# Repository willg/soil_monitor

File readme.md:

# Soil Monitor
Three different probes to monitor the moisture of soil by measuring the
capacitance.  

# Probe Testing

Connected multimeter to the 3 different probe designs as follows:

Extech 470 -> dual banana jack -> ~6" dupont M-F hookup wire -> header on
probe soldered to `In+` and `GND`.  This setup with no probe measured 0.18nF.

| Measurement | Design A | Design B | Design C
| ---         | ---      | ---      | ---       |
| Free Space | 0.19 nF  |  0.19 nF | 0.22 nF
| Water |     0.75 nF    |  0.90 nF | 0.83 nF
| Delta | 0.56 nF | 0.71 nF | 0.61 nF

## CAM
To generate gerbers download
[kicad-util](https://gitlab.com/dren.dk/kicad-util) and run the following to
add mouse bites where the lines on `Eco1.User`.  
```
java -jar kicadutil.jar pcb
--file=soil_monitor.kicad_pcb panel --fillet=1
```

This will create the file `output.soil_monitor.kicad_pcb` from which the
gerbers are created

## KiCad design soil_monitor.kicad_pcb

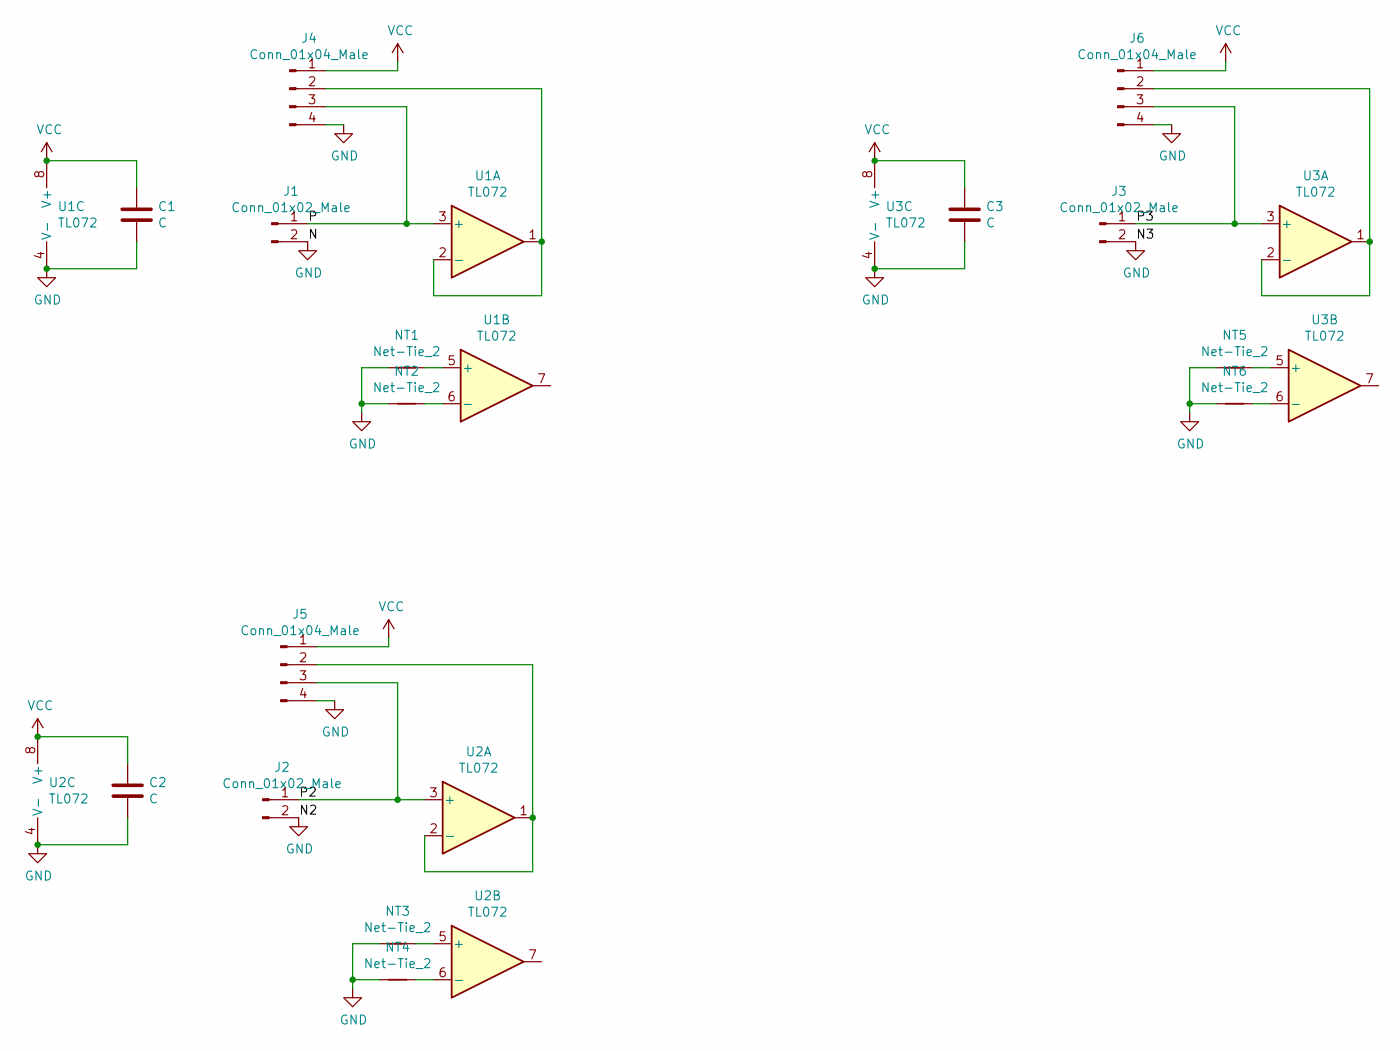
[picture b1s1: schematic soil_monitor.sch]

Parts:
C1, C2, C3: C; C_0805_2012Metric
J1, J2, J3: Conn_01x02_Male; PinHeader_1x02_P2.54mm_Vertical
J4, J5, J6: Conn_01x04_Male; PinSocket_1x04_P2.54mm_Vertical
NT1, NT2, NT3, NT4, NT5, NT6: Net-Tie_2; NetTie-2_SMD_Pad0.5mm
U1, U2, U3: TL072; DIP-8_W7.62mm

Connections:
/P: J1.1, J4.3, U1.3 (+)
/P2: J2.1, J5.3, U2.3 (+)
/P3: J3.1, J6.3, U3.3 (+)
GND: C1.2, C2.2, C3.2, J1.2, J2.2, J3.2, J4.4, J5.4, J6.4, NT1.1, NT2.1, NT3.1, NT4.1, NT5.1, NT6.1, U1.4 (V-), U2.4 (V-), U3.4 (V-)
unnamed: J4.2, U1.1, U1.2 (-)
unnamed: J5.2, U2.1, U2.2 (-)
unnamed: J6.2, U3.1, U3.2 (-)
unnamed: NT1.2, U1.5 (+)
unnamed: NT2.2, U1.6 (-)
unnamed: NT3.2, U2.5 (+)
unnamed: NT4.2, U2.6 (-)
unnamed: NT5.2, U3.5 (+)
unnamed: NT6.2, U3.6 (-)
VCC: C1.1, C2.1, C3.1, J4.1, J5.1, J6.1, U1.8 (V+), U2.8 (V+), U3.8 (V+)

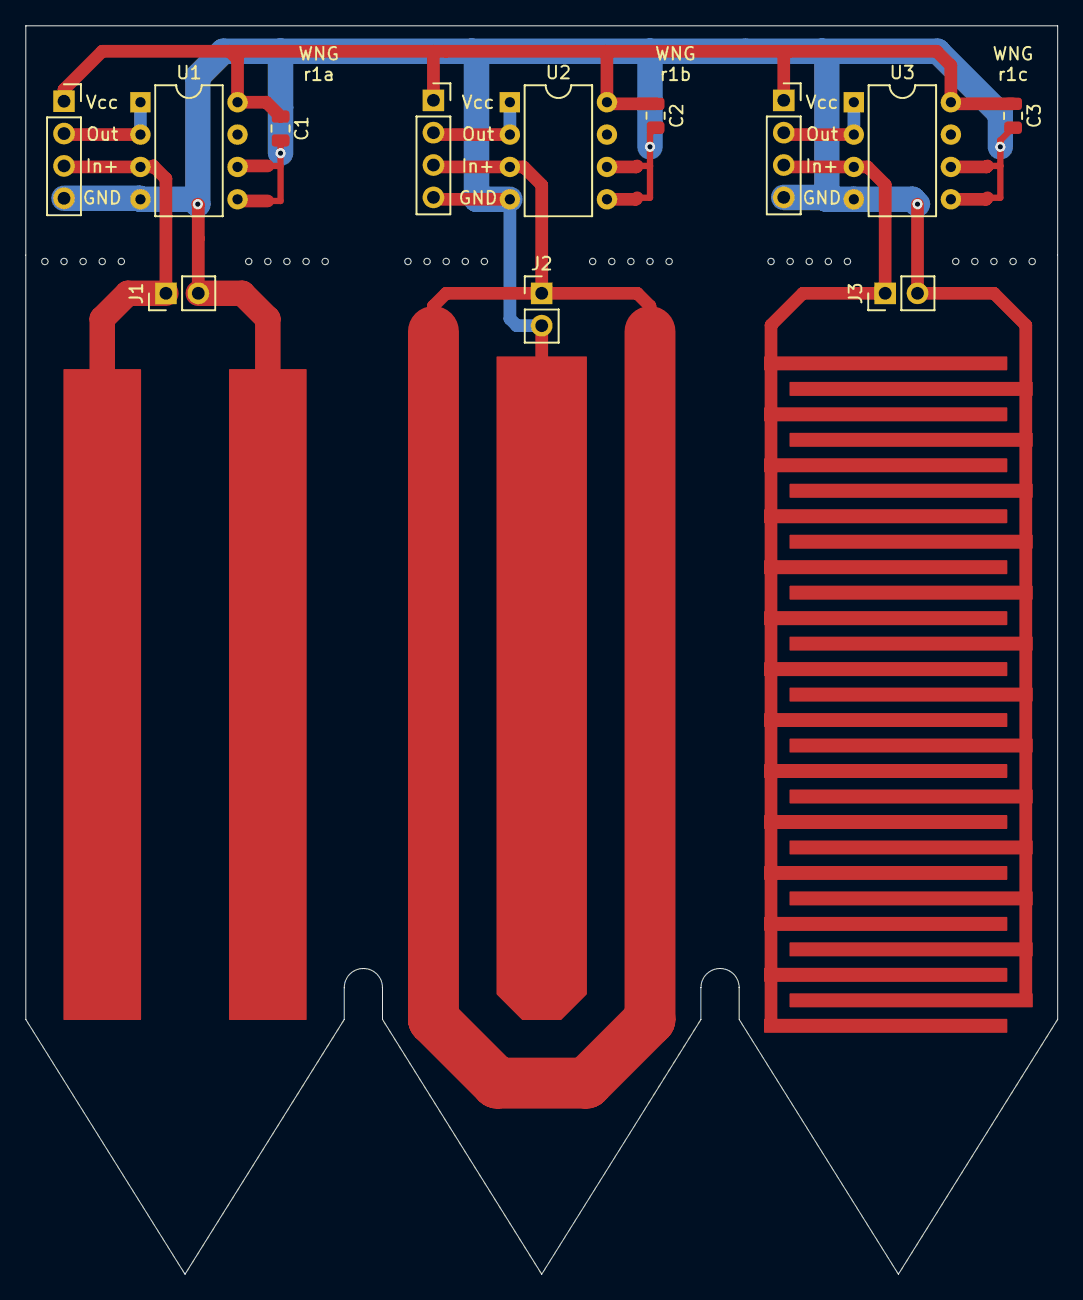
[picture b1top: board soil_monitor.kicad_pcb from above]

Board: 2 copper layers, 81.0 x 98.0 mm, 18 parts (0 on the bottom side), 14 nets.

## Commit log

2020-05-15 add readme
2020-05-15 add output file generated per readme
2020-05-22 added mouses bites, packaged files for fab
2020-05-31 fix like wrap
2020-05-31 add table with measurement results
2020-05-31 formatting
